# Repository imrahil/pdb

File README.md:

Power distribution board by Imrahil
===

Simple power distribution board for Reprap. Dimensions are 5x5 cm so it's perfect for Seeedstudio PCB service.

OSHW logo - http://oshwlogo.com/

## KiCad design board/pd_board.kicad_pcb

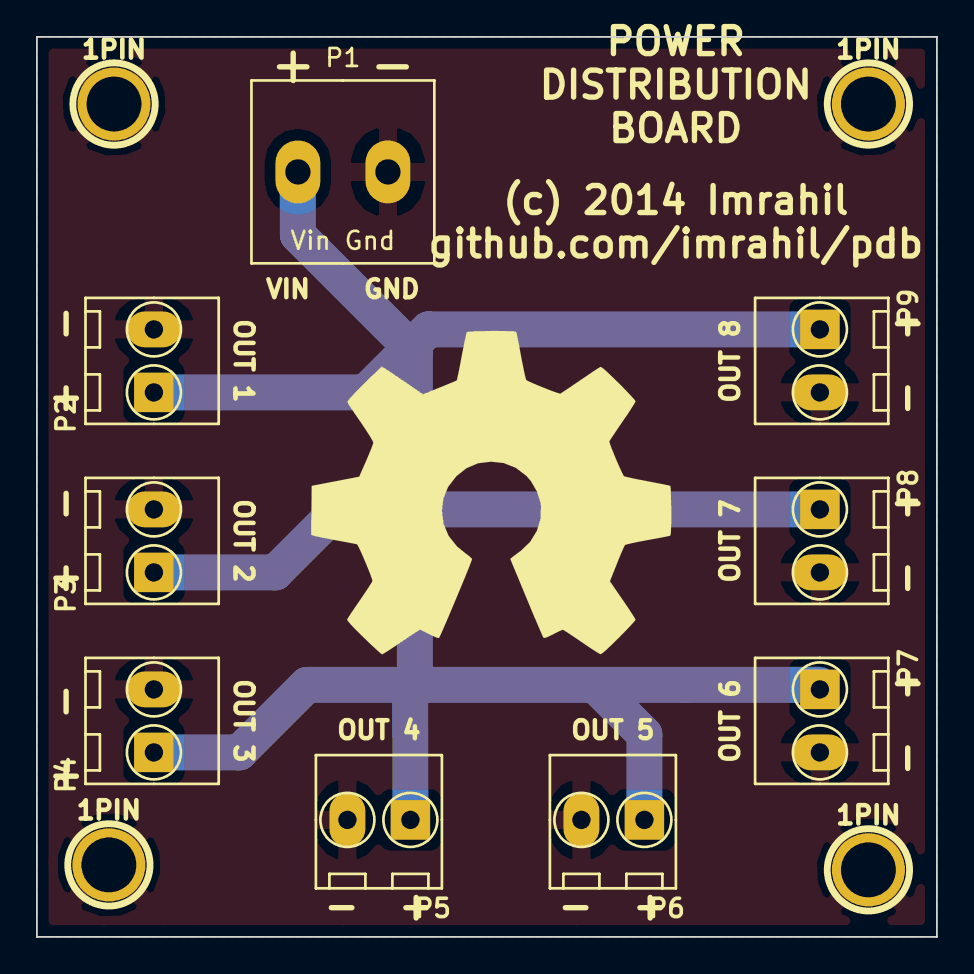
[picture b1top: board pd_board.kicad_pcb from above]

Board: 2 copper layers, 50.0 x 50.0 mm, 13 parts (0 on the bottom side), 2 nets.

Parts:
1PIN, 1PIN#2, 1PIN#3, 1PIN#4: P***; 1pin
P1: Vin Gnd; 2PIN-5mm
P2: OUT 1; TB-3,5x2
P3: OUT 2; TB-3,5x2
P4: OUT 3; TB-3,5x2
P5: OUT 4; TB-3,5x2
P6: OUT 5; TB-3,5x2
P7: OUT 6; TB-3,5x2
P8: OUT 7; TB-3,5x2
P9: OUT 8; TB-3,5x2

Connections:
GND: 1PIN.1, 1PIN#2.1, 1PIN#3.1, 1PIN#4.1, P1.2, P2.2, P3.2, P4.2, P5.2, P6.2, P7.2, P8.2, P9.2
VCC: P1.1, P2.1, P3.1, P4.1, P5.1, P6.1, P7.1, P8.1, P9.1

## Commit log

2014-04-14 Init - base version
2014-04-14 Board image
2014-04-14 Board image in README.md
2014-04-14 Basic info in README.md
2014-04-14 Resized pads, moved tracks to bottom layer
2014-04-15 Cleanup. Minor changes

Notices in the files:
board/pd_board.kicad_pcb:
(c) 2014 Imrahil
